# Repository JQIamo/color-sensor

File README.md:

# color-sensor

## Project Location
Find us on GitHub: http://git.io/vc8Iy or directly https://github.com/JQIamo/color-sensor/

 [color-sensor](https://github.com/JQIamo/color-sensor/) is licensed under a [Creative Commons Attribution-ShareAlike 4.0 International License](http://creativecommons.org/licenses/by-sa/4.0/).

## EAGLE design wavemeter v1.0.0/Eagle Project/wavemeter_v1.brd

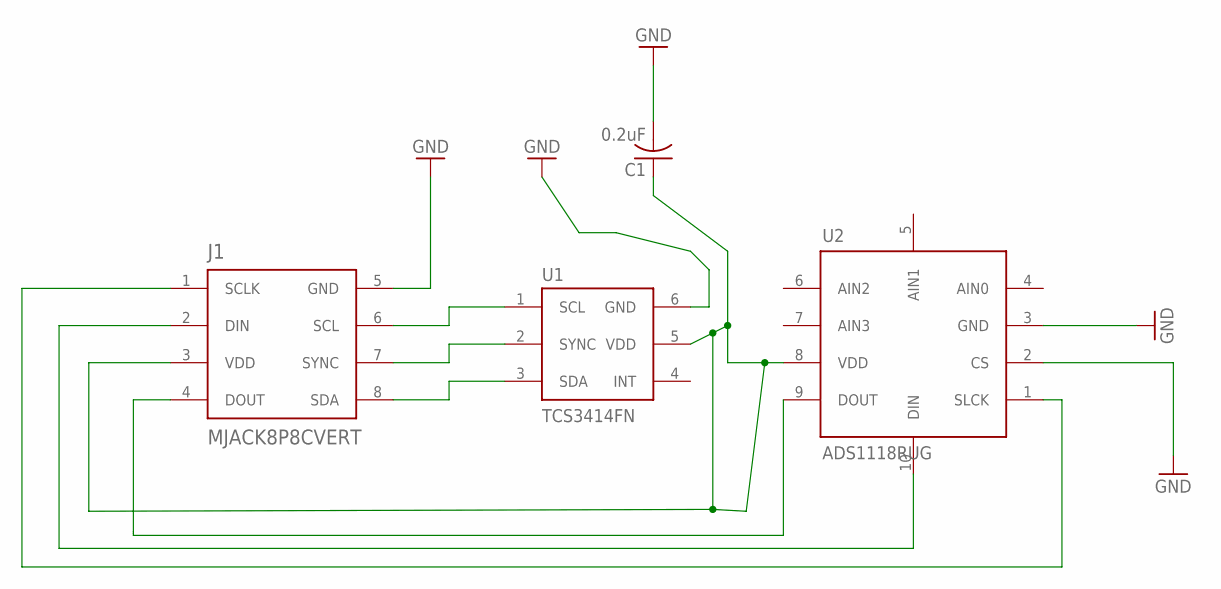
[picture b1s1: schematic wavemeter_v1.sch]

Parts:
C1: 0.2uF; C0603
J1: MJACK8P8CVERT; MJACK8P8C
U1: TCS3414FN; TCS3414
U2: ADS1118RUG; ADS1118

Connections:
GND: C1.2, J1.5 (GND), U1.6 (GND), U2.2 (CS), U2.3 (GND)
unnamed: J1.6 (SCL), U1.1 (SCL)
unnamed: J1.7 (SYNC), U1.2 (SYNC)
unnamed: J1.8 (SDA), U1.3 (SDA)
unnamed: C1.1, J1.3 (VDD), U1.5 (VDD), U2.8 (VDD)
unnamed: J1.4 (DOUT), U2.9 (DOUT)
unnamed: J1.2 (DIN), U2.10 (DIN)
unnamed: J1.1 (SCLK), U2.1 (SLCK)

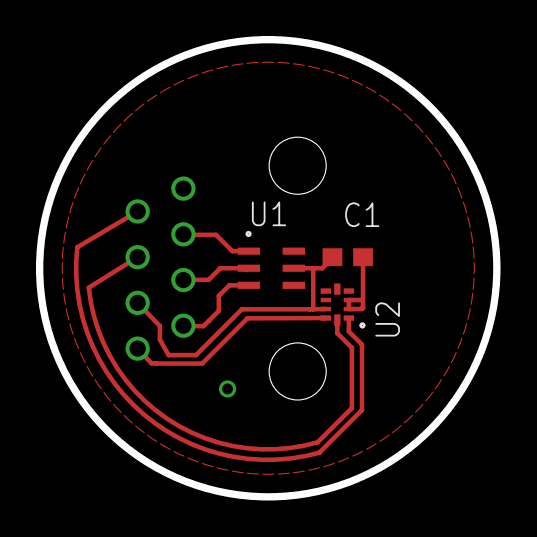
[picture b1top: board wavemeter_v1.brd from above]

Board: 2 copper layers, 25.4 x 25.4 mm, 4 parts (1 on the bottom side), 8 nets.

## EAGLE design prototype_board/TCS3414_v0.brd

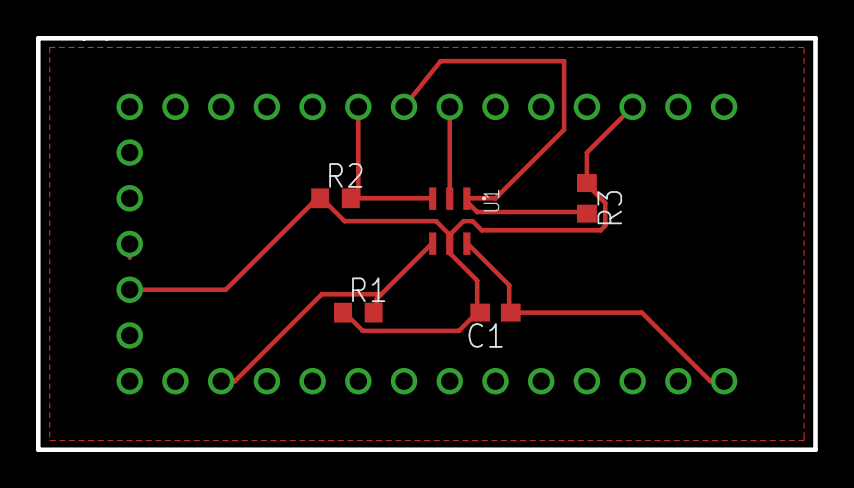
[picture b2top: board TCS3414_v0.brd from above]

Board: 2 copper layers, 43.2 x 22.9 mm, 6 parts (1 on the bottom side), 6 nets.

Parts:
C1: 0.1uF; C0603
R1: 10k; R0603
R2, R3: 4k7; R0603
U1: TCS3414FNFN; TCS3414FN
U$1: TEENSY_3.1_BASIC

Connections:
GND: C1.1, U1.6, U$1.GND, U$1.GND1
unnamed: R1.2, U1.4, U$1.10
unnamed: R2.2, U1.3, U$1.18/A4
unnamed: R3.2, U1.1, U$1.19/A5
unnamed: U1.2, U$1.20/A6
VDD: C1.2, R1.1, R2.1, R3.1, U1.5, U$1.3.3V, U$1.3.3V1

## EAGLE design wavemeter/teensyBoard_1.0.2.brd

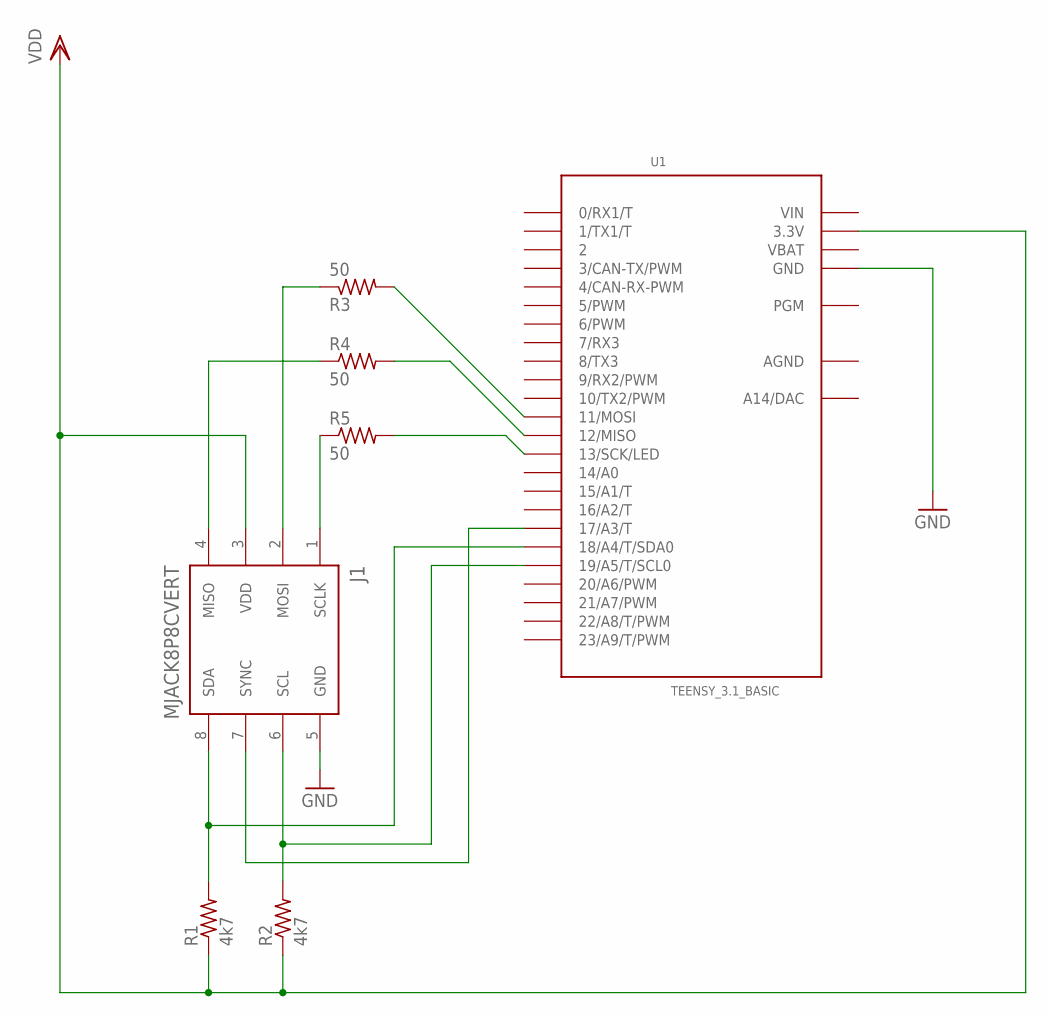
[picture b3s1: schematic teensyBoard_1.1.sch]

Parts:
J1: MJACK8P8CVERT; MJACK8P8C
R1, R2: 4k7; R0603
R3, R4, R5: 50; R0603
U1: TEENSY_3.1_BASIC

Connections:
AGND: U1.AGND
GND: J1.5 (GND), U1.GND, U1.GND1 (GND)
unnamed: R3.2, U1.11 (11/MOSI)
unnamed: J1.6 (SCL), R2.2, U1.19/A5 (19/A5/T/SCL0)
unnamed: J1.4 (MISO), R4.1
unnamed: R4.2, U1.12 (12/MISO)
unnamed: J1.1 (SCLK), R5.1
unnamed: R5.2, U1.13 (13/SCK/LED)
unnamed: J1.8 (SDA), R1.2, U1.18/A4 (18/A4/T/SDA0)
unnamed: J1.7 (SYNC), U1.17/A3 (17/A3/T)
unnamed: J1.2 (MOSI), R3.1
VBAT: U1.VBAT
VDD: J1.3 (VDD), R1.1, R2.1, U1.3.3V, U1.3.3V1 (3.3V)
VIN: U1.VIN

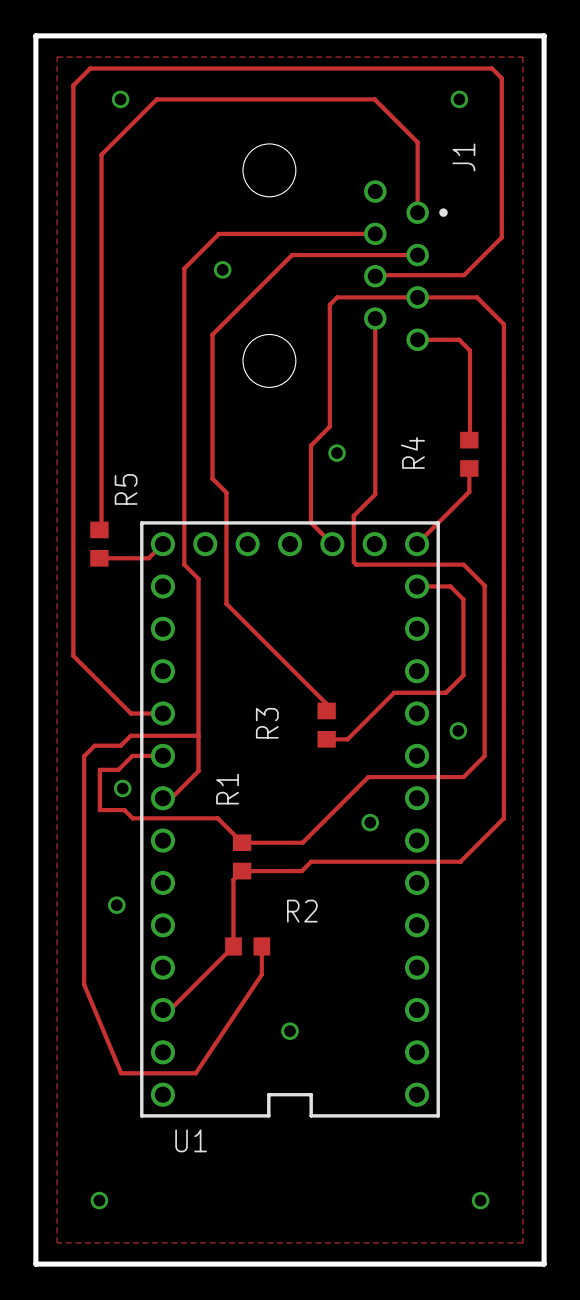
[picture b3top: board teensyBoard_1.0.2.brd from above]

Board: 2 copper layers, 30.5 x 73.7 mm, 7 parts (0 on the bottom side), 11 nets.

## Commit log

2015-09-30 Update README.md
    Added link back to the GitHub repository.
2015-09-30 Create LICENSE.md
    Creative Commons v4.0 Share-Alike
2015-09-30 Update README.md
    Add badge for creative-commons license.
2015-10-01 Initial layout for Eagle Project
    Includes library containing QR code linking to the project on GitHub.
2015-10-01 Add Logo Library
2015-10-01 Add datasheets
2015-10-01 Add Eagle Description for lbr directory
2015-10-04 Add Aaron's Prototype Board
    Includes his generated TCS3414 library as well as the first schematic
    and layout for testing the color sensor.
    Also has mcu-accessories.lbr from the JQIamo/mcu-accessories repository.
2015-10-06 Changed resistor values
    2.5k to 10k and 1.3k to 4.7k resistor changes
2015-10-15 Color sensor circuit Arduino code
    Currently grabs 4 readings per second with a 100us integration cycle
2015-10-16 Updated version of sensor data gathering program
    Nothing major, mostly style changes
2015-10-20 Adding new Arduino code with sync functionality for sensor chip
    New file w sync functionality
2015-11-17 Production v1.0.0
    Eagle schematic, board, and library files (also added datasheets for new
    parts ADS1118 and Ethernet Jack)
2016-01-28 Clean up and organization of folders
    Also fixed crossed MOSI/MISO wires on the teensyBoard eagle files
2016-01-28 Updated Eagle files
    Fixed crossed wires on teensyBoard
2016-02-01 Fixed time sync code
2016-03-02 New Eagle layout
    Moved all wiring to top of board
2016-03-04 Sensor data runs

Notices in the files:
README.md:
License: Creative Commons BY-SA 4.0
